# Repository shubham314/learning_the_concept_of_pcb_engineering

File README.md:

# learning_the_concept_of_pcb_engineering
pcb engineering data

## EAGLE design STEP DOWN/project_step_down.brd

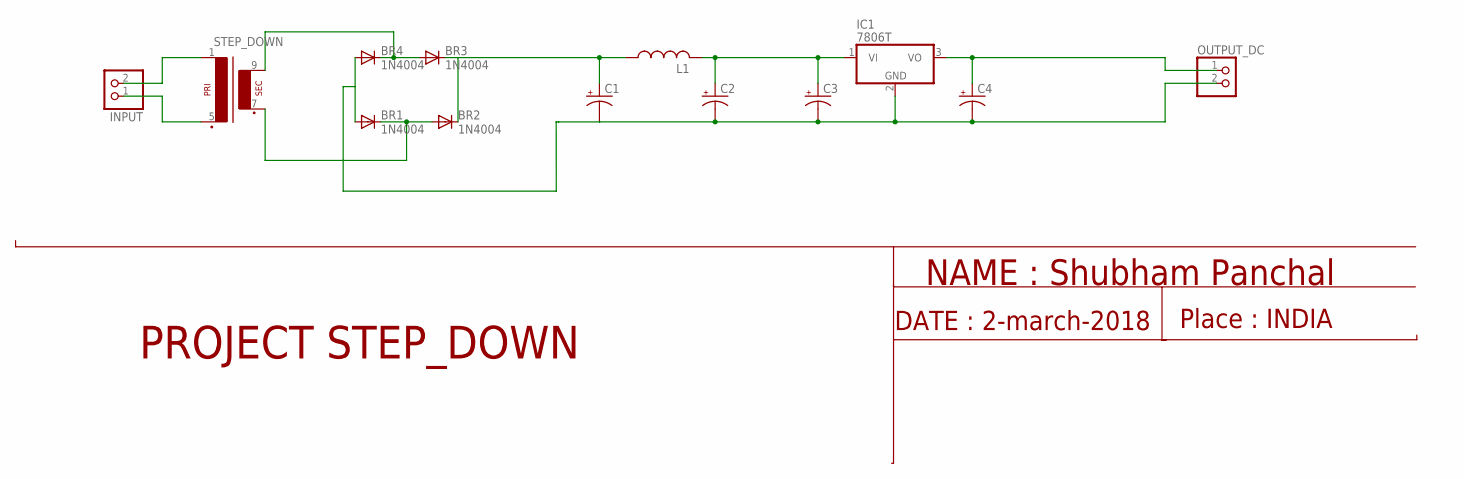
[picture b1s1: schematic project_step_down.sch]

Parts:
BR1, BR2, BR3, BR4: 1N4004; DO41-10
C1, C2, C3, C4: CPOL-USE2.5-7; E2,5-7
IC1: 7806T; TO220H
INPUT: PINHD-1X2; 1X02
L1: L-US0204/7; 0204/7
OUTPUT_DC: PINHD-1X2; 1X02
STEP_DOWN: EI30-1

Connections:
GND: C1.-, C2.-, C3.-, C4.-, IC1.2 (GND), OUTPUT_DC.2
unnamed: INPUT.2, STEP_DOWN.1
unnamed: INPUT.1, STEP_DOWN.5 (P2)
unnamed: BR3.A, BR4.C, STEP_DOWN.9 (S4)
unnamed: BR1.C, BR2.A, STEP_DOWN.7 (S3)
unnamed: BR1.A, BR4.A
unnamed: BR2.C, BR3.C, C1.+, L1.1
unnamed: C2.+, C3.+, IC1.1 (VI), L1.2
unnamed: C4.+, IC1.3 (VO), OUTPUT_DC.1

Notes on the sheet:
PROJECT STEP_DOWN
NAME : Shubham Panchal
DATE : 2-march-2018
Place : INDIA

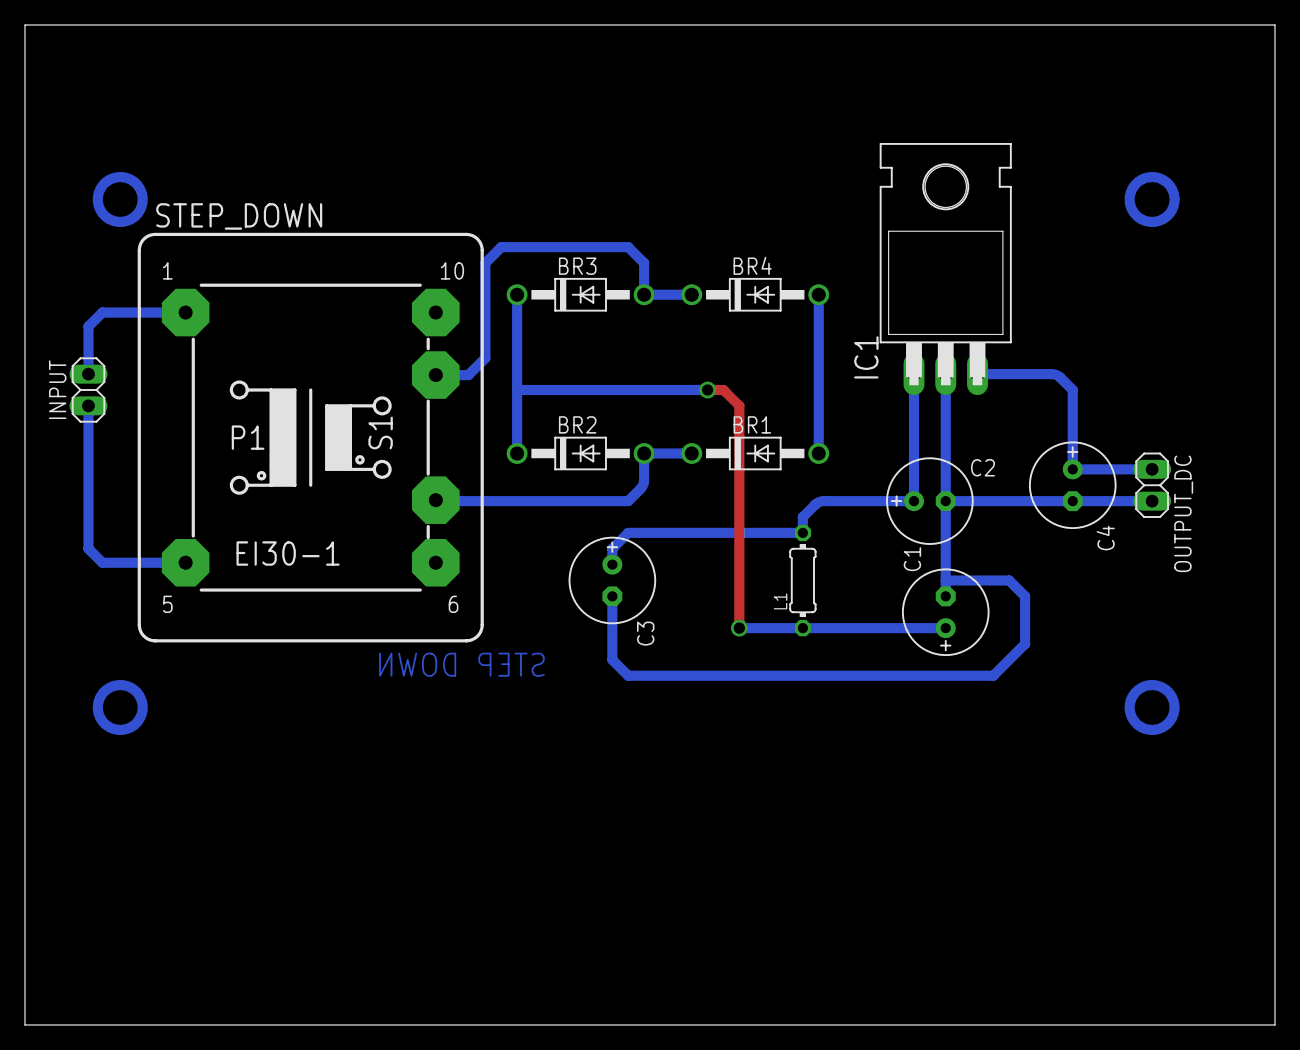
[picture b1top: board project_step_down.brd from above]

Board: 2 copper layers, 100.0 x 80.0 mm, 13 parts (0 on the bottom side), 9 nets.

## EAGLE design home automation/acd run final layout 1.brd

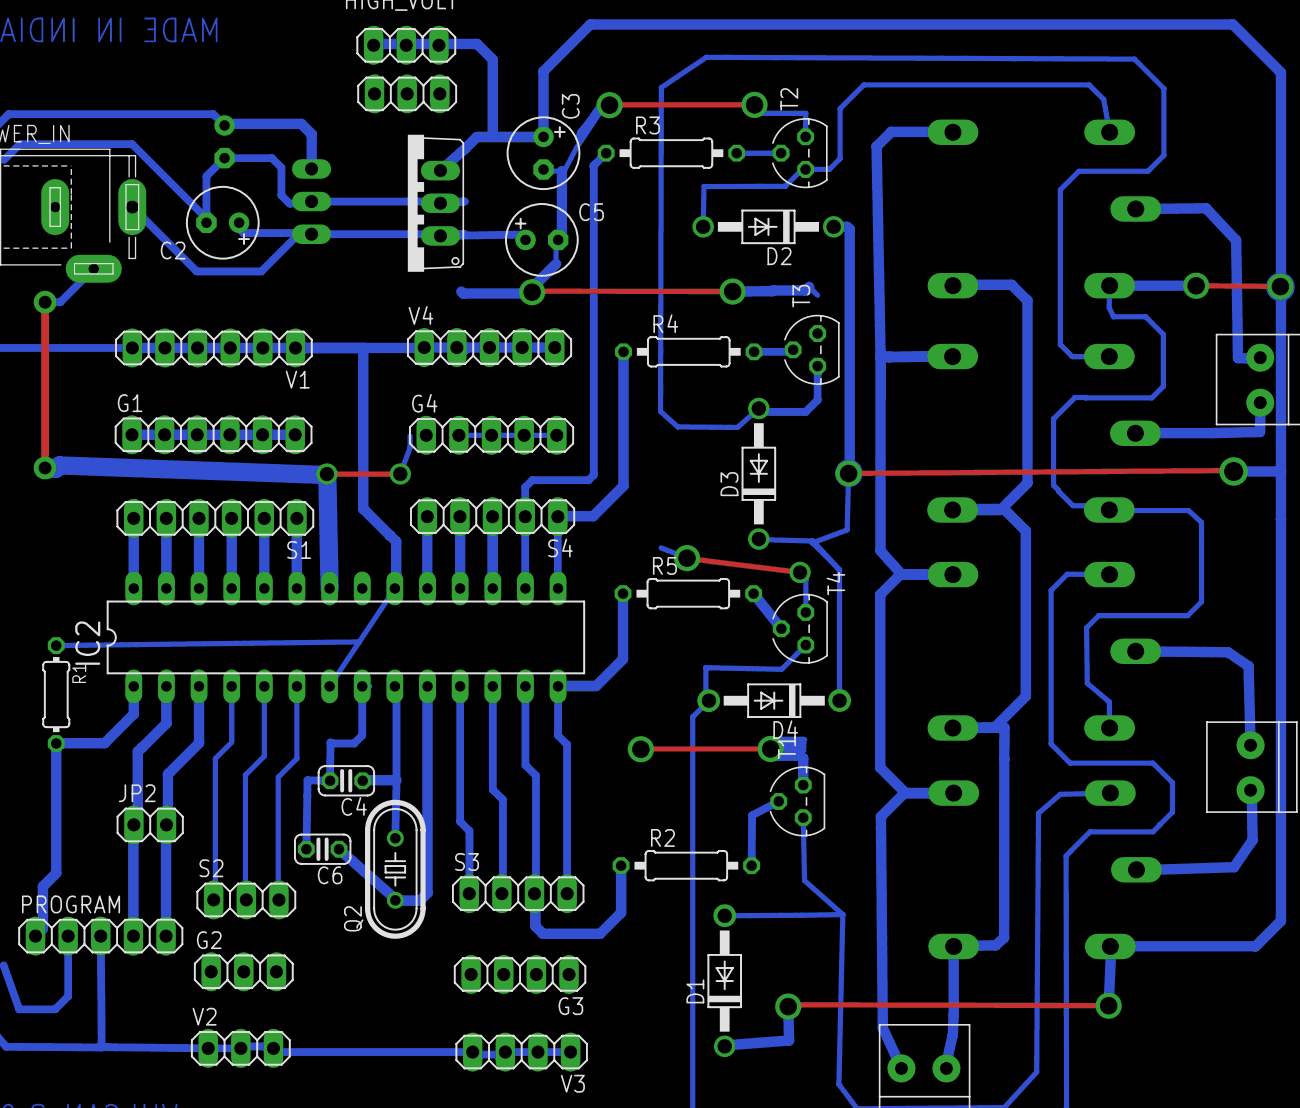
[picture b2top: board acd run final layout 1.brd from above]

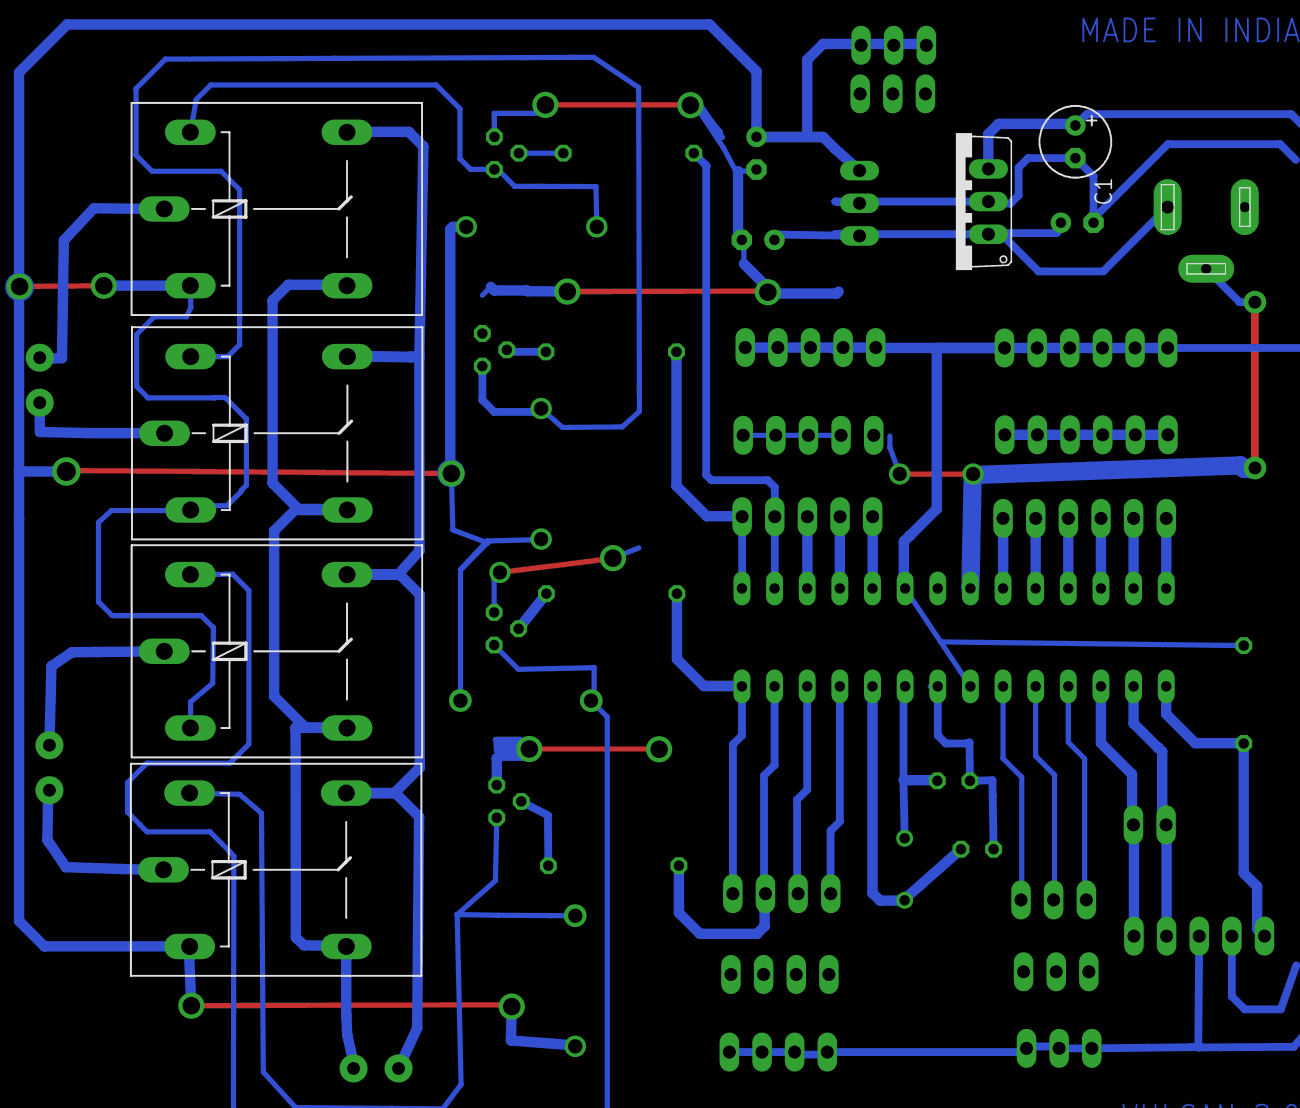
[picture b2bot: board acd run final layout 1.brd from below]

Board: 2 copper layers, 47 parts (6 on the bottom side), 40 nets.

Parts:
BATTERY: 1X2-3.5MM
C1, C2, C3, C5: E2,5-6
C4, C6: C025-024X044
D1, D2, D3, D4: 1N4004; DO41-10
G1: 1X06
G2: 1X03
G3: 1X04
G4: 1X05
GATE_1, GATE_2: 1X2-3.5MM
HIGH_VOLT: 1X03
IC1, IC4: 7812TV; TO220V
IC2: MEGA8-P; DIL28-3
JP1: 1X03
JP2: 1X02
K1, K2, K3, K4: G5LE
POWER_IN: SPC4077
PROGRAM: 1X05
Q2: HC49/S
R1: 0204/7
R2, R3, R4, R5: 0207/10
S1: 1X06
S2: 1X03
S3: 1X04
S4: 1X05
T1, T2, T3, T4: BC547; TO92
V1: 1X06
V2: 1X03
V3: 1X04
V4: 1X05

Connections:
+5V: C1.+, IC2.7, IC2.20, IC4.3, PROGRAM.3, R1.1, V1.1, V1.2, V1.3, V1.4, V1.5, V1.6, V2.1, V2.2, V2.3, V3.1, V3.2, V3.3, V3.4, V4.1, V4.2, V4.3, V4.4, V4.5
GND: C1.-, C2.-, C3.-, C5.-, G1.1, G1.2, G1.3, G1.4, G1.5, G1.6, G2.1, G2.2, G2.3, G3.1, G3.2, G3.3, G3.4, G4.1, G4.2, G4.3, G4.4, G4.5, IC1.2, IC2.22, IC4.2, JP1.1, JP1.2, JP1.3, POWER_IN.2, PROGRAM.2, T1.1, T2.1, T3.1, T4.1
IPJUMPERS: IC2.1, PROGRAM.1, R1.2
unnamed: C4.1, IC2.9, Q2.2
unnamed: C6.1, IC2.10, Q2.1
unnamed: IC2.28, S1.6
unnamed: IC2.27, S1.5
unnamed: IC2.6, S2.3
unnamed: C3.+, D1.C, HIGH_VOLT.1, HIGH_VOLT.2, HIGH_VOLT.3, IC1.3, K4.1
unnamed: IC2.26, S1.4
unnamed: IC2.25, S1.3
unnamed: IC2.24, S1.2
unnamed: IC2.23, S1.1
unnamed: IC2.19, S4.5
unnamed: IC2.5, S2.2
unnamed: IC2.18, S4.4
unnamed: IC2.17, S4.3
unnamed: IC2.16, R3.1, S4.2
unnamed: IC2.14, R5.1, S3.4
unnamed: IC2.13, R2.1, S3.3
unnamed: D1.A, K4.2, T1.3
unnamed: D2.A, K1.2, T2.3
unnamed: D3.A, K2.2, T3.3
unnamed: IC2.4, S2.1
unnamed: IC2.3, JP2.2, PROGRAM.5
unnamed: IC2.2, JP2.1, PROGRAM.4
unnamed: K1.O, K2.O, K3.O, K4.O
unnamed: C2.+, C5.+, IC1.1, IC4.1, POWER_IN.3
unnamed: IC2.15, R4.1, S4.1
unnamed: D4.A, K3.2, T4.3
unnamed: K1.S, K2.S, K3.S, K4.S
unnamed: R5.2, T4.2
unnamed: R4.2, T3.2
unnamed: IC2.12, S3.2
unnamed: R3.2, T2.2
unnamed: R2.2, T1.2
unnamed: IC2.11, S3.1
S$25: K1.1, K2.1, K3.1
S$26: D2.C, D3.C, D4.C
S$28: C4.2, C6.2, IC2.8

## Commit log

2018-03-08 Add files via upload
    All the files are related with PCB CAD,feel free to use it.
